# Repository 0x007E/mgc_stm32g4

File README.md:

# `MGC_module` - STM32G4

The `STM32G4` (`mgc_module`) is an adaptable board for the [MeGARCard](https://github.com/0x007e/mgc). The board offers the possibility to control the `MeGARCard` with an [STM32G4](#additional-information). The board itself is connected to the `MeGARCard` within the pcb-to-pcb connectors (no soldering necessary). With the onboard dip-switches the board voltage can be regulated from `3V3` to `5V`. Also the usage of hardware-/software-`twi` to control the [SSD1306](#additional-information)-display on the megacard can be selected.

> To mount the board on the `MeGARCard` disconnect the power source (`USB-C` connector) or any other used source from the MeGARCard!

| Experience  | Level                                                                               |
|:------------|:-----------------------------------------------------------------------------------:|
| Soldering   |  |

# Downloads

| Type      | File                                                                                                                                                 | Description     |
|:---------:|:----------------------------------------------------------------------------------------------------------------------------------------------------:|:----------------|
| Schematic | [pdf](https://github.com/0x007E/mgc_stm32g4/releases/latest/download/schematic.pdf) / [cadlab](https://cadlab.io/project/30728/main/files)                   | Schematic files |
| Board     | [pdf](https://github.com/0x007E/mgc_stm32g4/releases/latest/download/pcb.pdf) / [cadlab](https://cadlab.io/project/30728/main/files)                         | Board file      |
| Drill     | [pdf](https://github.com/0x007E/mgc_stm32g4/releases/latest/download/drill.pdf)                                                                              | Drill file      |
| BoM | [xlsx](https://github.com/0x007E/mgc_stm32g4/releases/latest/download/bom.xlsx) / [html](https://github.com/0x007E/mgc_stm32g4/releases/latest/download/ibom.html)          | Bill of Material as Excel/interactive HTML |
| PCB    | [zip](https://github.com/0x007E/mgc_stm32g4/releases/latest/download/kicad.zip) / [tar](https://github.com/0x007E/mgc_stm32g4/releases/latest/download/kicad.tar.gz)    | KiCAD/Gerber/BoM/Drill files       |

# Hardware

The pcb is created with `KiCAD`. All files are built with `github actions` so that they are ready for a production environment.

## PCB

The circuit board is populated on both sides (Top, Bottom). The best way for soldering the `SMD` components is within a vapor phase soldering system and for the `THT` components with a standard soldering system.

### Top Layer

### Bottom Layer

# Additional Information

| Type       | Link               | Description              |
|:----------:|:------------------:|:-------------------------|
| STM32G4  | [pdf](https://www.st.com/resource/en/datasheet/stm32g491cc.pdf) | Arm® Cortex®-M4 32-bit MCU+FPU, 170 MHz / 213 DMIPS |
| SSD1306 | [pdf](https://www.vishay.com/docs/37902/oled128o064dbpp3n00000.pdf) | 128 x 64 Graphic OLED |

---

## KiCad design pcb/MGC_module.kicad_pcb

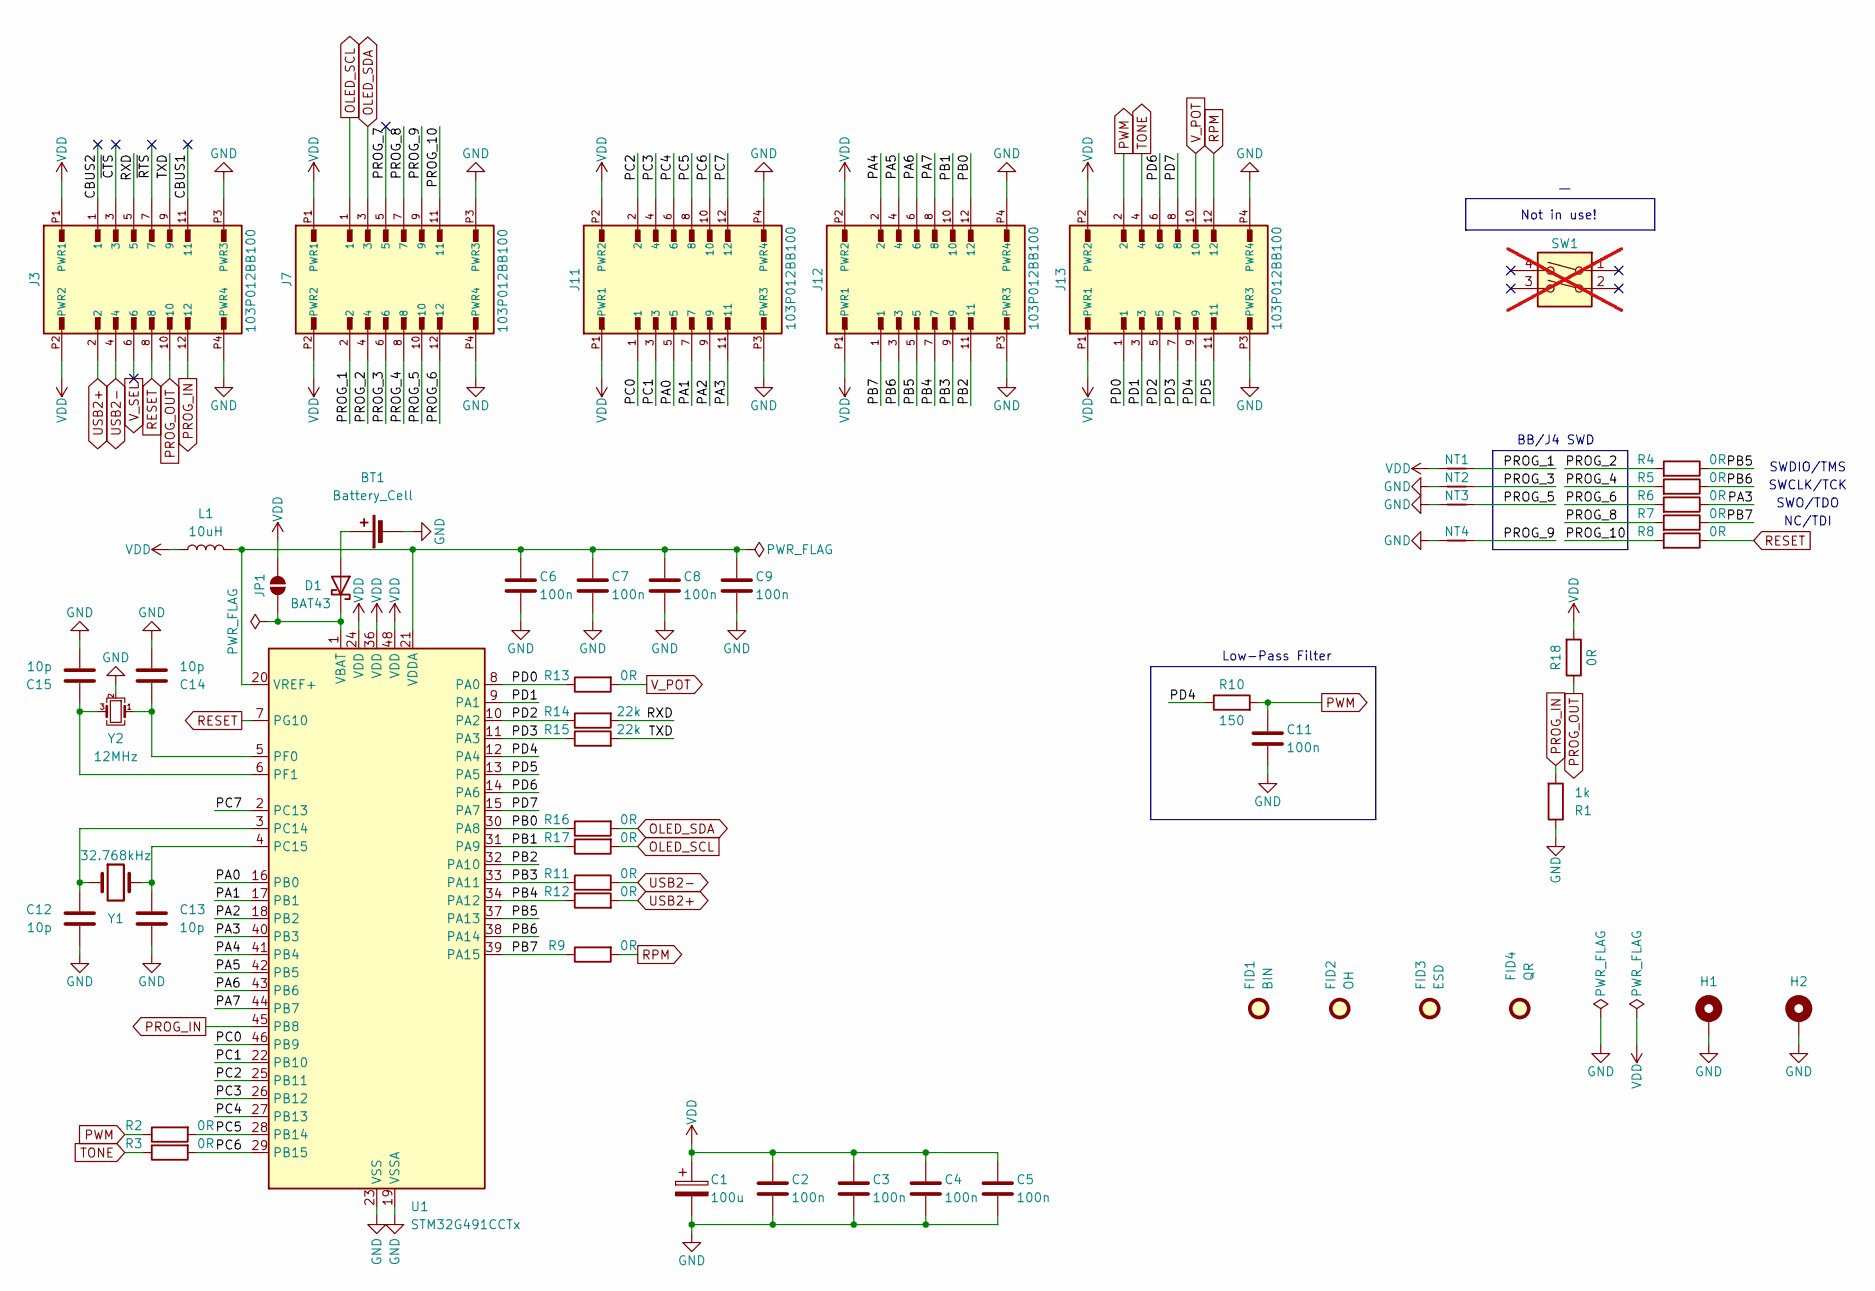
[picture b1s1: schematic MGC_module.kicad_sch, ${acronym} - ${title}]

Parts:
BT1: Battery_Cell; BatteryHolder_LINX_BAT-HLD-012-SMT
C1: 100u; CP_EIA-3528-21_Kemet-B; DigiKey 478-3877-1-ND
C2, C3, C4, C5, C6, C7, C8, C9, C11: 100n; C_1206_3216Metric
C12, C13, C14, C15: 10p; C_0603_1608Metric
D1: BAT43; D_MiniMELF
FID1: BIN; WEEE-Logo_4.2x6mm_SilkScreen
FID2: OH; OSHW-Logo2_7.3x6mm_SilkScreen
FID3: ESD; ESD-Logo_6.6x6mm_SilkScreen
FID4: QR; QR_0x007e_very_small
H1, H2: MountingHole_Pad; MountingHole_2.7mm_M2.5_DIN965_Pad
J3, J7, J11, J12, J13: 103P012BB100; AMPHENOL_103P012BB100; DigiKey 609-103P012BB100CT-ND
JP1: SolderJumper_2_Open; SolderJumper-2_P1.3mm_Open_RoundedPad1.0x1.5mm
L1: 10uH; L_1206_3216Metric
NT1, NT2, NT3, NT4: NetTie_2; NetTie-2_SMD_Pad0.5mm
R1: 1k; R_1206_3216Metric
R2, R3, R4, R5, R6, R7, R8, R9, R13, R16, R17, R18: 0R; R_1206_3216Metric
R10: 150; R_1206_3216Metric
R11, R12: 0R; R_0603_1608Metric; DigiKey CR0603AJ/-000EASCT-ND
R14, R15: 22k; R_1206_3216Metric
SW1: SW_DIP_x02; SW_DIP_SPSTx02_Slide_6.7x6.64mm_W6.73mm_P2.54mm_LowProfile_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; not fitted
U1: STM32G491CCTx; LQFP-48_7x7mm_P0.5mm; DigiKey 497-STM32G491CCT6-ND
Y1: 32.768kHz; Crystal_SMD_3215-2Pin_3.2x1.5mm
Y2: 12MHz; Crystal_SMD_Abracon_ABM8AIG-4Pin_3.2x2.5mm

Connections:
/CBUS1: J3.11
/CBUS2: J3.1
/PA0: J11.5, U1.16 (PB0)
/PA1: J11.7, U1.17 (PB1)
/PA2: J11.9, U1.18 (PB2)
/PA3: J11.11, R6.1, U1.40 (PB3)
/PA4: J12.2, U1.41 (PB4)
/PA5: J12.4, U1.42 (PB5)
/PA6: J12.6, U1.43 (PB6)
/PA7: J12.8, U1.44 (PB7)
/PB0: J12.12, R16.1, U1.30 (PA8)
/PB1: J12.10, R17.1, U1.31 (PA9)
/PB2: J12.11, U1.32 (PA10)
/PB3: J12.9, R11.1, U1.33 (PA11)
/PB4: J12.7, R12.1, U1.34 (PA12)
/PB5: J12.5, R4.1, U1.37 (PA13)
/PB6: J12.3, R5.1, U1.38 (PA14)
/PB7: J12.1, R7.1, R9.1, U1.39 (PA15)
/PC0: J11.1, U1.46 (PB9)
/PC1: J11.3, U1.22 (PB10)
/PC2: J11.2, U1.25 (PB11)
/PC3: J11.4, U1.26 (PB12)
/PC4: J11.6, U1.27 (PB13)
/PC5: J11.8, R2.2, U1.28 (PB14)
/PC6: J11.10, R3.2, U1.29 (PB15)
/PC7: J11.12, U1.2 (PC13)
/PD0: J13.1, R13.1, U1.8 (PA0)
/PD1: J13.3, U1.9 (PA1)
/PD2: J13.5, R14.1, U1.10 (PA2)
/PD3: J13.7, R15.1, U1.11 (PA3)
/PD4: J13.9, R10.1, U1.12 (PA4)
/PD5: J13.11, U1.13 (PA5)
/PD6: J13.6, U1.14 (PA6)
/PD7: J13.8, U1.15 (PA7)
/PROG_1: J7.2, NT1.1
/PROG_2: J7.4, R4.2
/PROG_3: J7.6, NT2.1
/PROG_4: J7.8, R5.2
/PROG_5: J7.10, NT3.1
/PROG_6: J7.12, R6.2
/PROG_7: J7.5
/PROG_8: J7.7, R7.2
/PROG_9: J7.9, NT4.1
/PROG_10: J7.11, R8.2
/RXD: J3.5, R14.2
/TXD: J3.9, R15.2
/~CTS: J3.3
/~RTS: J3.7
GND: BT1.2 (-), C1.2, C2.2, C3.2, C4.2, C5.2, C6.2, C7.2, C8.2, C9.2, C11.2, C12.2, C13.2, C14.2, C15.2, H1.1, H2.1, J3.P3 (PWR3), J3.P4 (PWR4), J7.P3 (PWR3), J7.P4 (PWR4), J11.P3 (PWR3), J11.P4 (PWR4), J12.P3 (PWR3), J12.P4 (PWR4), J13.P3 (PWR3), J13.P4 (PWR4), NT2.2, NT3.2, NT4.2, R1.1, U1.19 (VSSA), U1.23 (VSS), U1.35 (VSS), U1.47 (VSS), Y2.2 (G), Y2.4 (G)
unnamed: BT1.1 (+), D1.2 (A)
unnamed: D1.1 (K), JP1.1 (A), U1.1 (VBAT)
unnamed: C12.1, U1.3 (PC14), Y1.1
unnamed: C13.1, U1.4 (PC15), Y1.2
unnamed: C14.1, U1.5 (PF0), Y2.1
unnamed: C15.1, U1.6 (PF1), Y2.3
unnamed: C6.1, C7.1, C8.1, C9.1, L1.2, U1.20 (VREF+), U1.21 (VDDA)
OLED_SCL: J7.1, R17.2
OLED_SDA: J7.3, R16.2
PROG_IN: J3.12, R1.2, U1.45 (PB8)
PROG_OUT: J3.10, R18.1
PWM: C11.1, J13.2, R2.1, R10.2
RESET: J3.8, R8.1, U1.7 (PG10)
RPM: J13.12, R9.2
TONE: J13.4, R3.1
USB2+: J3.2, R12.2
USB2-: J3.4, R11.2
VDD: C1.1, C2.1, C3.1, C4.1, C5.1, J3.P1 (PWR1), J3.P2 (PWR2), J7.P1 (PWR1), J7.P2 (PWR2), J11.P1 (PWR1), J11.P2 (PWR2), J12.P1 (PWR1), J12.P2 (PWR2), J13.P1 (PWR1), J13.P2 (PWR2), JP1.2 (B), L1.1, NT1.2, R18.2, U1.24 (VDD), U1.36 (VDD), U1.48 (VDD)
V_POT: J13.10, R13.2
V_SEL: J3.6

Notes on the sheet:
Not in use!
SWCLK/TCK
Low-Pass Filter
SWO/TDO
NC/TDI
SWDIO/TMS
BB/J4 SWD

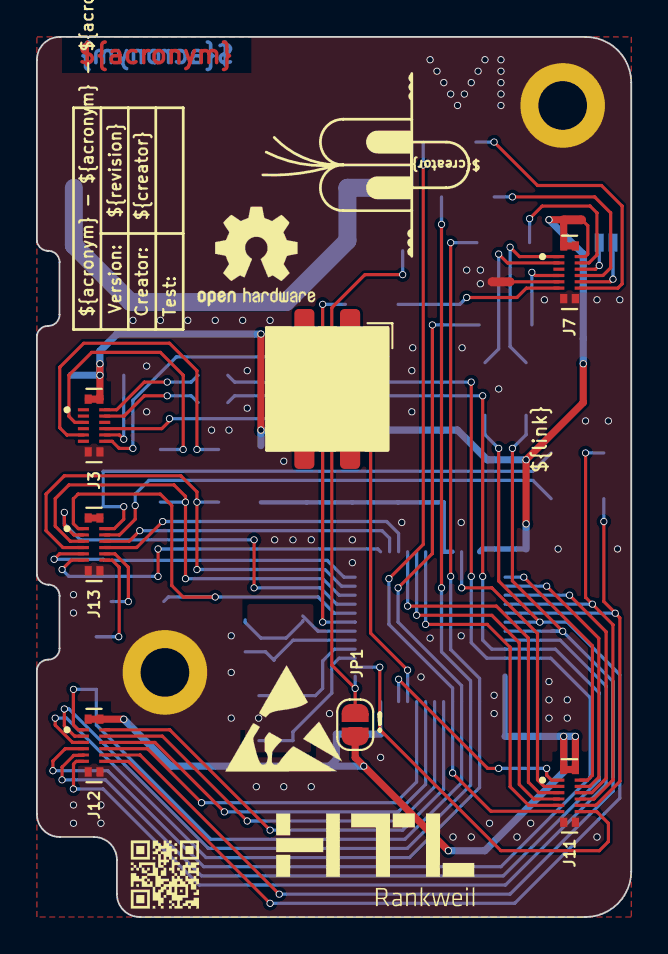
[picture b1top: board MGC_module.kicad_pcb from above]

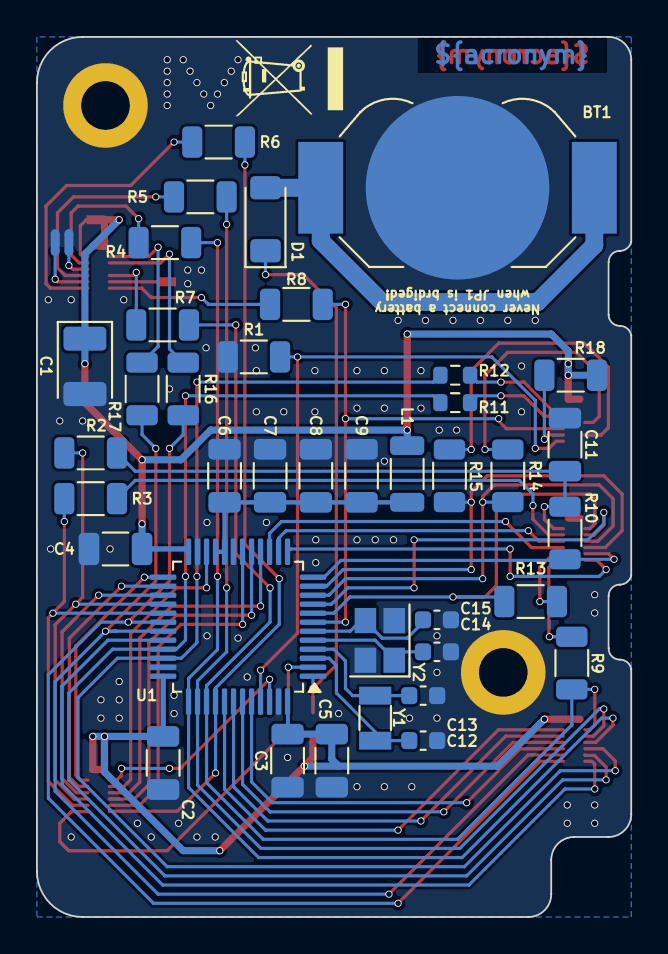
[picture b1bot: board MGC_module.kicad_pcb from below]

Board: 2 copper layers, 33.0 x 48.9 mm, 55 parts (41 on the bottom side), 63 nets.

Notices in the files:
README.md:
License CC By-NC-SA
parts and their libraries:
license: CC BY-NC-SA 4.0
